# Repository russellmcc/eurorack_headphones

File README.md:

This is a tested design for a small headphone amp/line output module for eurorack modular synthesizers.

Most of the construction is SMT, with the exception of user-replaceable socketted op-amps.

Please use the BOM.txt to order parts.

This is 5hp and uses 20mA current.

This work is licensed under a [Creative Commons Attribution-ShareAlike 3.0 Unported License.](http://creativecommons.org/licenses/by-sa/3.0/deed.en_US)

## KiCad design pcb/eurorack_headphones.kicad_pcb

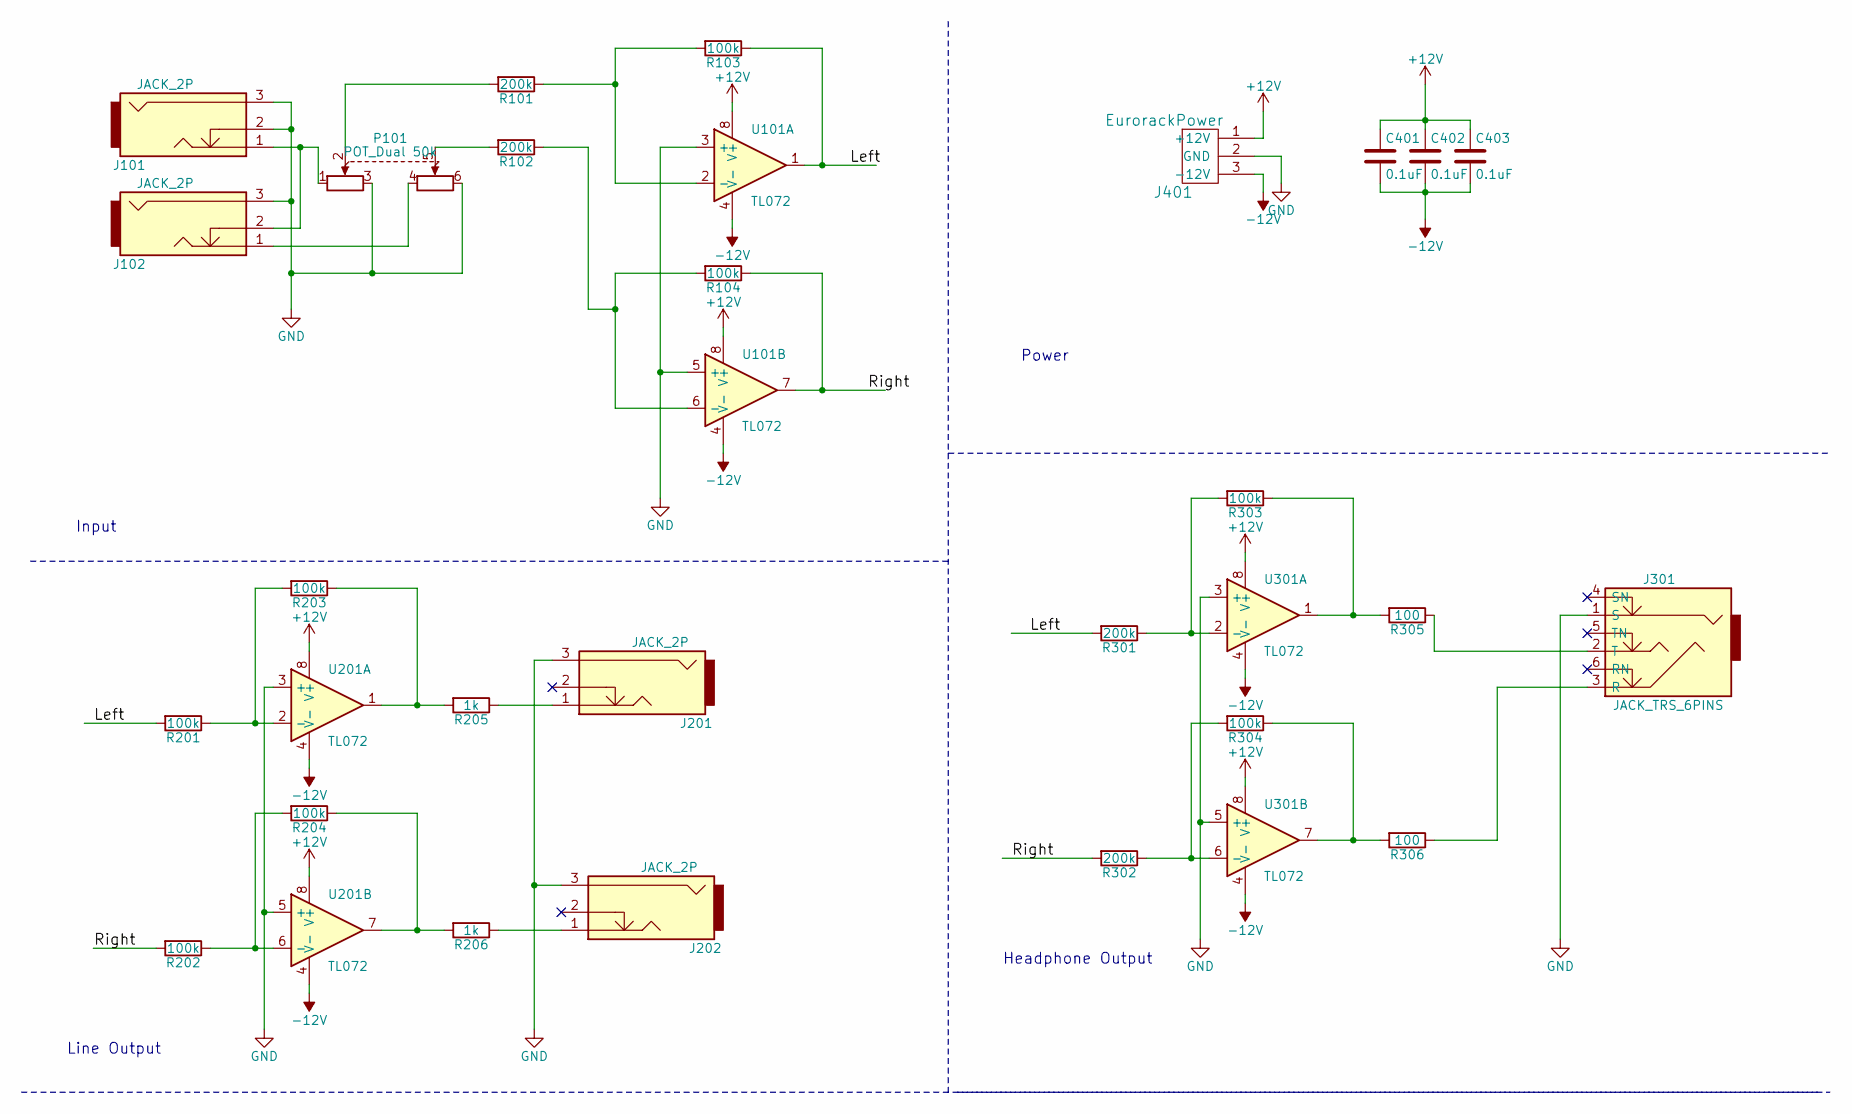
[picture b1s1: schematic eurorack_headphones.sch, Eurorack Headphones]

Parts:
C401, C402, C403: 0.1uF; C_0603_HandSoldering
J101, J102: JACK_2P; Jack.PJ302M
J201, J202: JACK_2P; Neutrick_NMJ4HHD2
J301: JACK_TRS_6PINS; Neutrick_NMJ4HFD2
J401: EurorackPower; EurorackPower10
P101: POT_Dual 50k; ALPS_RK09_Horizontal
R101, R102, R301, R302: 200k; R_0603_HandSoldering
R103, R104, R201, R202, R203, R204, R303, R304: 100k; R_0603_HandSoldering
R205, R206: 1k; R_0603_HandSoldering
R305, R306: 100; R_0603_HandSoldering
U101: TL072; SOIC-8_3.9x4.9mm_Pitch1.27mm
U201, U301: TL072; DIP-8_W7.62mm_Socket

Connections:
+12V: C401.1, C402.1, C403.1, J401.1 (+12V), U101.8 (V+), U201.8 (V+), U301.8 (V+)
-12V: C401.2, C402.2, C403.2, J401.3 (-12V), U101.4 (V-), U201.4 (V-), U301.4 (V-)
/Left: R103.1, R201.2, R301.2, U101.1
/Right: R104.1, R202.2, R302.2, U101.7
GND: J101.2, J101.3, J102.3, J201.3, J202.3, J301.1 (S), J401.2 (GND), P101.3, P101.6, U101.3 (+), U101.5 (+), U201.3 (+), U201.5 (+), U301.3 (+), U301.5 (+)
unnamed: J101.1, J102.2, P101.1
unnamed: J102.1, P101.4
unnamed: J201.1, R205.1
unnamed: J202.1, R206.1
unnamed: J301.2 (T), R305.1
unnamed: J301.3 (R), R306.1
unnamed: P101.2, R101.2
unnamed: P101.5, R102.2
unnamed: R101.1, R103.2, U101.2 (-)
unnamed: R102.1, R104.2, U101.6 (-)
unnamed: R201.1, R203.2, U201.2 (-)
unnamed: R202.1, R204.2, U201.6 (-)
unnamed: R203.1, R205.2, U201.1
unnamed: R204.1, R206.2, U201.7
unnamed: R301.1, R303.2, U301.2 (-)
unnamed: R302.1, R304.2, U301.6 (-)
unnamed: R303.1, R305.2, U301.1
unnamed: R304.1, R306.2, U301.7

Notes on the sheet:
Input
Line Output
Headphone Output
Power

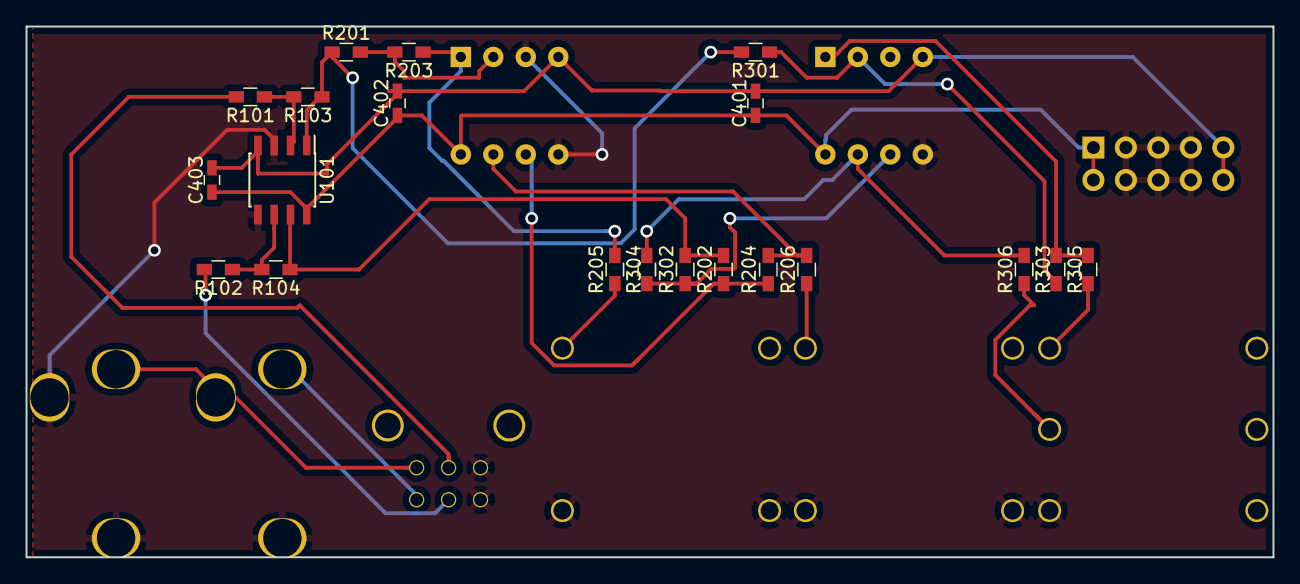
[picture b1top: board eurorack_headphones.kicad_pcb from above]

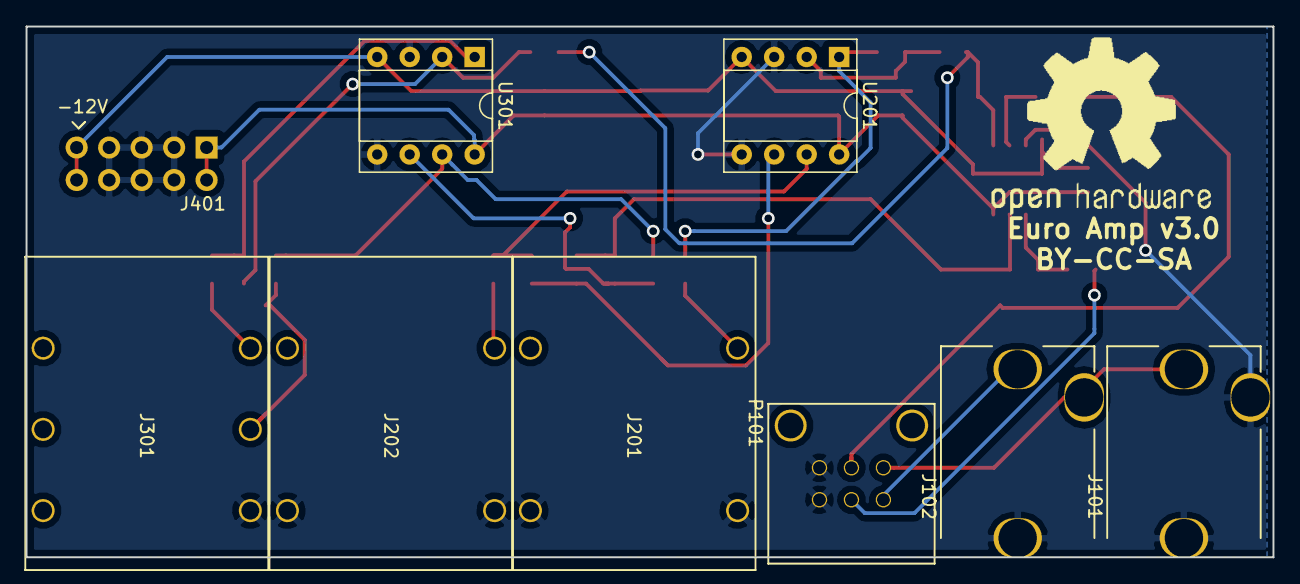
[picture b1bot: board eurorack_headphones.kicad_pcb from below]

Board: 2 copper layers, 97.5 x 41.5 mm, 29 parts (9 on the bottom side), 23 nets.

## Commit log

2013-02-06 initial version of headphone amp
2013-02-07 Added gitignore and a BOM
2013-02-07 Added README with CC license
2013-02-07 finished parting out the BOM from mouser
2013-02-14 added silkscreen
2013-02-14 layers
2013-02-14 Panel!
2013-03-14 solder mask!
2013-04-08 fix for backwards volume knob and too-small text
2013-04-08 fixed front panel
2013-05-15 update readme with specs
2017-06-08 WIP new kicad design
2017-06-08 Update panel
2017-06-08 Update pcb
2017-06-08 Fix for BOM
2017-06-29 Fix errors on board
